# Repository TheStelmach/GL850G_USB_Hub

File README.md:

Board made primarily for evaluation of the GL852G IC that was at the time being considered for a larger PCB design.
Contains one High-Speed upstream port and four independent downstream HS/FS ports with MTT.

Designed for easy hand assembly, with only two 0402 capacitors for crystal. All bootstrapping and IO pins are easily accessible on the board.

Components are only placed on top layer.

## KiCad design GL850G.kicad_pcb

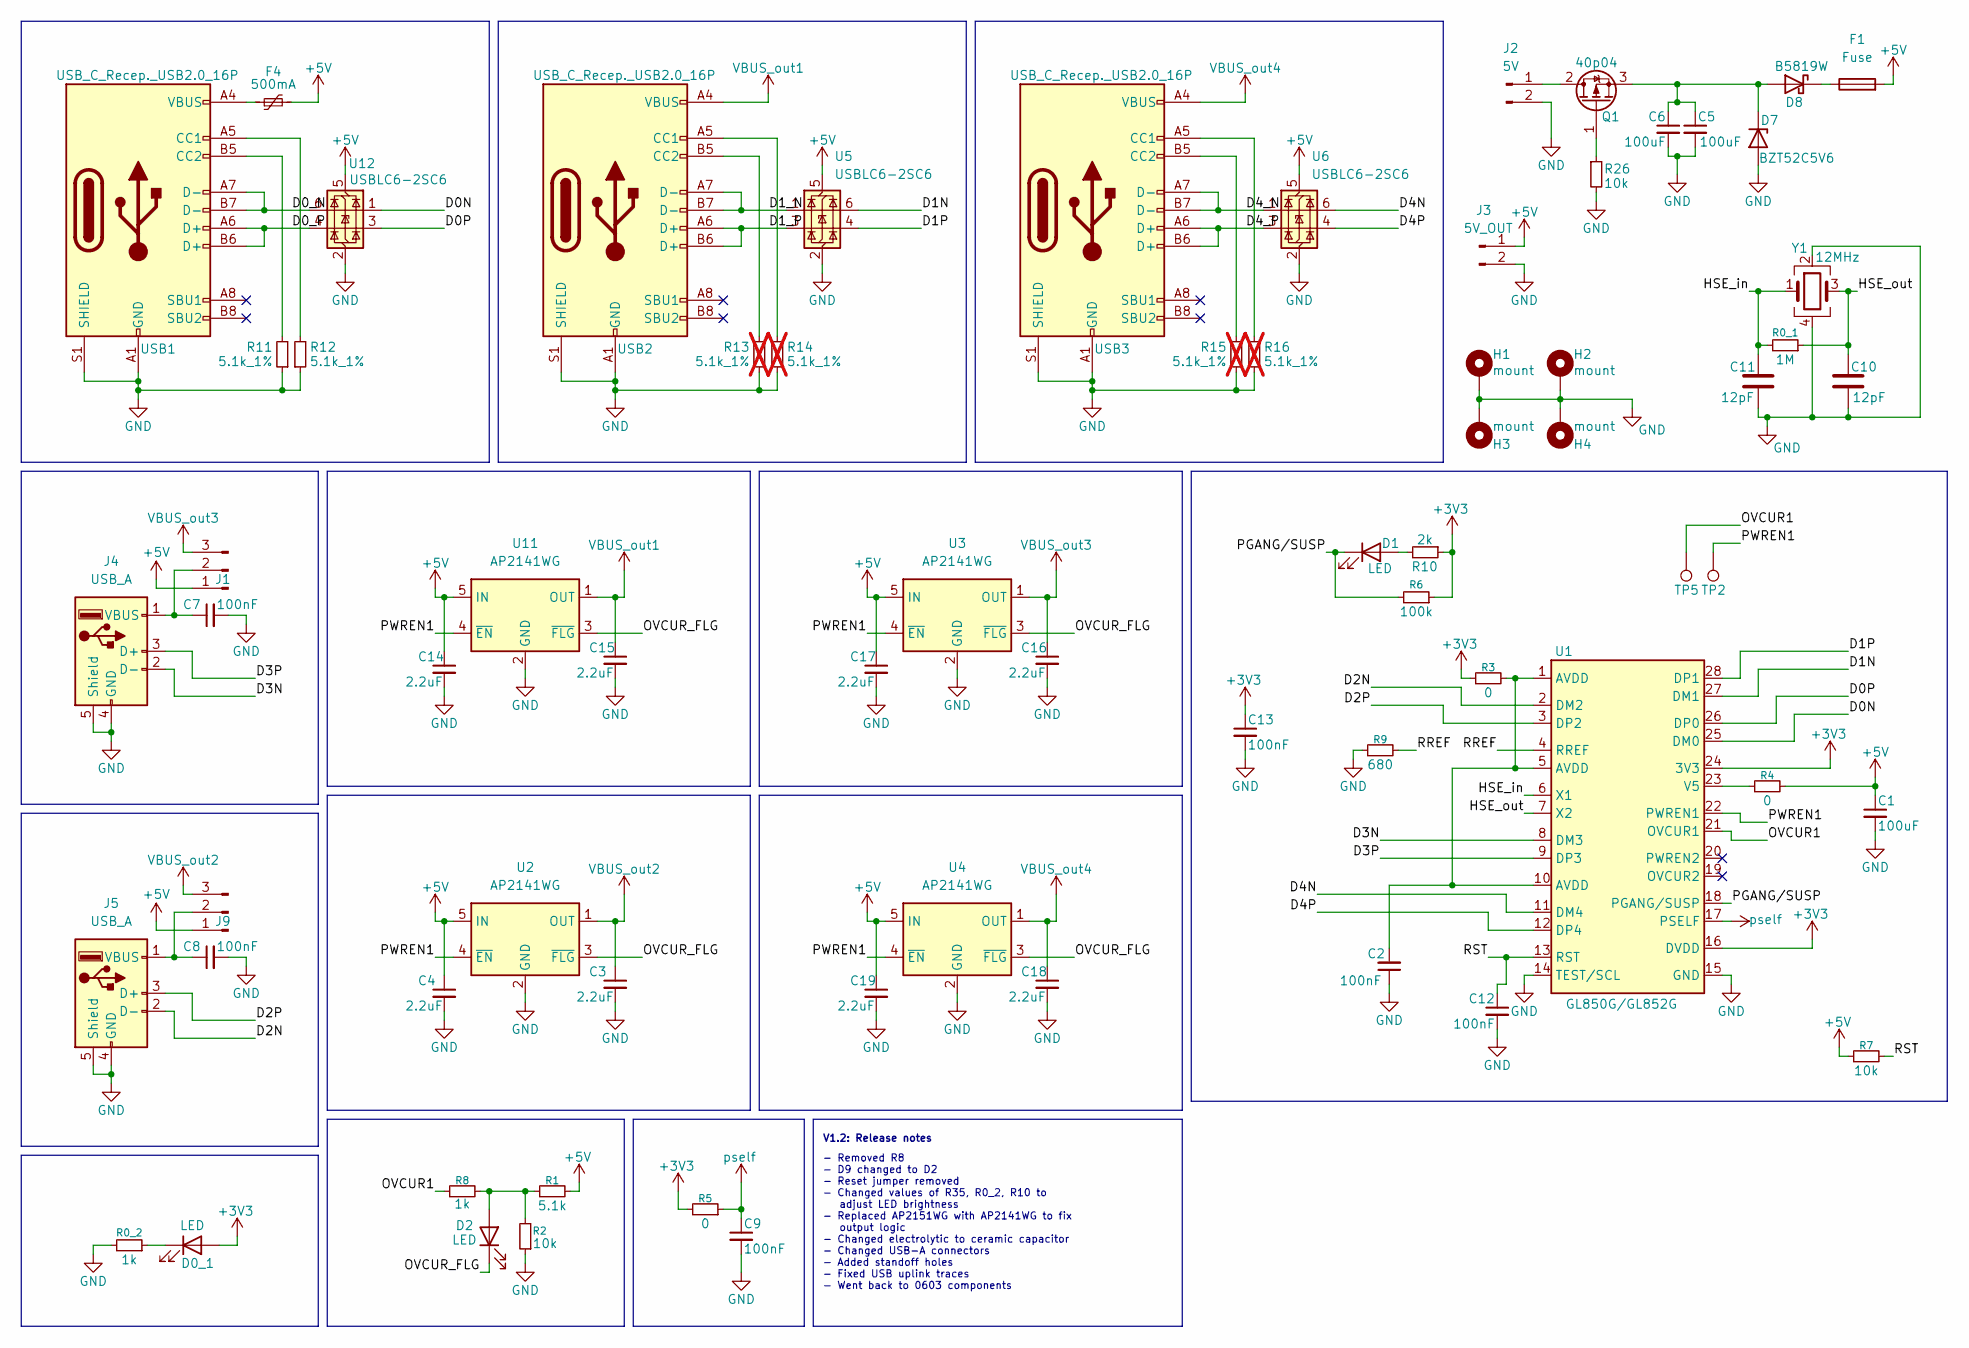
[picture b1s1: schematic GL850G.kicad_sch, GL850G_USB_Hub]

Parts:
C1, C5, C6: 100uF; C_1206_3216Metric_Pad1.33x1.80mm_HandSolder
C2, C7, C8, C9, C12, C13: 100nF; C_0603_1608Metric_Pad1.08x0.95mm_HandSolder
C3, C4, C14, C15, C16, C17, C18, C19: 2.2uF; C_0603_1608Metric_Pad1.08x0.95mm_HandSolder
C10, C11: 12pF; C_0402_1005Metric_Pad0.74x0.62mm_HandSolder
D0_1, D1, D2: LED; LED_0805_2012Metric_Pad1.15x1.40mm_HandSolder
D7: BZT52C5V6; D_SOD-123
D8: B5819W; D_SOD-123
F1: Fuse; Fuseholder_Littelfuse_Nano2_154x
F4: 500mA; Fuse_0805_2012Metric
H1, H2, H3, H4: mount; Standoff_M2
J1, J9: Conn_01x03_Pin; PinHeader_1x03_P2.54mm_Vertical
J2: 5V; JST_XH_B2B-XH-A_1x02_P2.50mm_Vertical
J3: 5V_OUT; PinHeader_1x02_P2.54mm_Vertical
J4, J5: USB_A; USB_2.0_TYPE_A_RECESSED
Q1: 40p04; TO-252-2
R0_1: 1M; R_0805_2012Metric_Pad1.20x1.40mm_HandSolder
R0_2: 1k; R_0603_1608Metric_Pad0.98x0.95mm_HandSolder
R1: 5.1k; R_0805_2012Metric_Pad1.20x1.40mm_HandSolder
R2, R7: 10k; R_0805_2012Metric_Pad1.20x1.40mm_HandSolder
R3, R4, R5: 0; R_0805_2012Metric_Pad1.20x1.40mm_HandSolder
R6: 100k; R_0805_2012Metric_Pad1.20x1.40mm_HandSolder
R8: 1k; R_0805_2012Metric_Pad1.20x1.40mm_HandSolder
R9: 680; R_0805_2012Metric_Pad1.20x1.40mm_HandSolder
R10: 2k; R_0805_2012Metric_Pad1.20x1.40mm_HandSolder
R11, R12: 5.1k_1%; R_0603_1608Metric_Pad0.98x0.95mm_HandSolder
R13, R14, R15, R16: 5.1k_1%; R_0603_1608Metric_Pad0.98x0.95mm_HandSolder; not fitted
R26: 10k; R_0603_1608Metric_Pad0.98x0.95mm_HandSolder
TP2, TP5: TestPoint; TestPoint_Pad_D2.0mm
U1: GL850G/GL852G; SSOP-28_5.3x10.2mm_P0.65mm
U2, U3, U4, U11: AP2141WG; SOT-23-5_HandSoldering
U5, U6, U12: USBLC6-2SC6; SOT-23-6
USB1, USB2, USB3: USB_C_Recep._USB2.0_16P; USB_C_Receptacle_GCT_USB4105-xx-A_16P_TopMnt_Horizontal
Y1: 12MHz; Crystal_SMD_3225-4Pin_3.2x2.5mm_HandSoldering

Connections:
+3V3: C13.1, D0_1.2 (A), R3.1, R5.2, R6.1, R10.1, U1.16 (DVDD), U1.24 (3V3)
+5V: C1.1, C4.1, C14.1, C17.1, C19.1, F1.2, F4.2, J1.1, J3.1, J9.1, R1.2, R4.2, R7.1, U2.5 (IN), U3.5 (IN), U4.5 (IN), U5.5 (VBUS), U6.5 (VBUS), U11.5 (IN), U12.5 (VBUS)
/D0N: U1.25 (DM0), U12.1 (I/O1)
/D0P: U1.26 (DP0), U12.3 (I/O2)
/D0_N: U12.6 (I/O1), USB1.A7 (D-), USB1.B7 (D-)
/D0_P: U12.4 (I/O2), USB1.A6 (D+), USB1.B6 (D+)
/D1N: U1.27 (DM1), U5.6 (I/O1)
/D1P: U1.28 (DP1), U5.4 (I/O2)
/D1_N: U5.1 (I/O1), USB2.A7 (D-), USB2.B7 (D-)
/D1_P: U5.3 (I/O2), USB2.A6 (D+), USB2.B6 (D+)
/D2N: J5.2 (D-), U1.2 (DM2)
/D2P: J5.3 (D+), U1.3 (DP2)
/D3N: J4.2 (D-), U1.8 (DM3)
/D3P: J4.3 (D+), U1.9 (DP3)
/D4N: U1.11 (DM4), U6.6 (I/O1)
/D4P: U1.12 (DP4), U6.4 (I/O2)
/D4_N: U6.1 (I/O1), USB3.A7 (D-), USB3.B7 (D-)
/D4_P: U6.3 (I/O2), USB3.A6 (D+), USB3.B6 (D+)
/HSE_in: C11.1, R0_1.2, U1.6 (X1), Y1.1
/HSE_out: C10.1, R0_1.1, U1.7 (X2), Y1.3
/OVCUR1: R8.1, TP5.1, U1.21 (OVCUR1)
/OVCUR_FLG: D2.1 (K), U2.3 (~FLG), U3.3 (~FLG), U4.3 (~FLG), U11.3 (~FLG)
/PGANG/SUSP: D1.1 (K), R6.2, U1.18 (PGANG/SUSP)
/PWREN1: TP2.1, U1.22 (PWREN1), U2.4 (~EN), U3.4 (~EN), U4.4 (~EN), U11.4 (~EN)
/RREF: R9.2, U1.4 (RREF)
/RST: C12.1, R7.2, U1.13 (RST)
GND: C1.2, C2.1, C3.2, C4.2, C5.2, C6.2, C7.2, C8.2, C9.2, C10.2, C11.2, C12.2, C13.2, C14.2, C15.2, C16.2, C17.2, C18.2, C19.2, D7.2 (A), H1.1, H2.1, H3.1, H4.1, J2.2, J3.2, J4.4 (GND), J4.5 (Shield), J5.4 (GND), J5.5 (Shield), R0_2.2, R2.1, R9.1, R11.1, R12.1, R13.1, R14.1, R15.1, R16.1, R26.2, U1.14 (TEST/SCL), U1.15 (GND), U2.2 (GND), U3.2 (GND), U4.2 (GND), U5.2 (GND), U6.2 (GND), U11.2 (GND), U12.2 (GND), USB1.A1 (GND), USB1.A12 (GND), USB1.B1 (GND), USB1.B12 (GND), USB1.S1 (SHIELD), USB2.A1 (GND), USB2.A12 (GND), USB2.B1 (GND), USB2.B12 (GND), USB2.S1 (SHIELD), USB3.A1 (GND), USB3.A12 (GND), USB3.B1 (GND), USB3.B12 (GND), USB3.S1 (SHIELD), Y1.2, Y1.4
unnamed: C2.2, R3.2, U1.1 (AVDD), U1.5 (AVDD), U1.10 (AVDD)
unnamed: D0_1.1 (K), R0_2.1
unnamed: D1.2 (A), R10.2
unnamed: D2.2 (A), R1.1, R2.2, R8.2
unnamed: C5.1, C6.1, D7.1 (K), D8.2 (A), Q1.3 (S)
unnamed: D8.1 (K), F1.1
unnamed: F4.1, USB1.A4 (VBUS), USB1.A9 (VBUS), USB1.B4 (VBUS), USB1.B9 (VBUS)
unnamed: C7.1, J1.2, J4.1 (VBUS)
unnamed: J2.1, Q1.2 (D)
unnamed: C8.1, J5.1 (VBUS), J9.2
unnamed: Q1.1 (G), R26.1
unnamed: R4.1, U1.23 (V5)
unnamed: R12.2, USB1.A5 (CC1)
unnamed: R11.2, USB1.B5 (CC2)
unnamed: R14.2, USB2.A5 (CC1)
unnamed: R13.2, USB2.B5 (CC2)
unnamed: R16.2, USB3.A5 (CC1)
unnamed: R15.2, USB3.B5 (CC2)
VBUS_out1: C15.1, U11.1 (OUT), USB2.A4 (VBUS), USB2.A9 (VBUS), USB2.B4 (VBUS), USB2.B9 (VBUS)
VBUS_out2: C3.1, J9.3, U2.1 (OUT)
VBUS_out3: C16.1, J1.3, U3.1 (OUT)
VBUS_out4: C18.1, U4.1 (OUT), USB3.A4 (VBUS), USB3.A9 (VBUS), USB3.B4 (VBUS), USB3.B9 (VBUS)
pself: C9.1, R5.1, U1.17 (PSELF)

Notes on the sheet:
V1.2: Release notes
- Removed R8 - D9 changed to D2 - Reset jumper removed - Changed values of R35, R0_2, R10 to adjust LED brightness - Replaced AP2151WG with AP2141WG to fix output logic - Changed electrolytic to ceramic capacitor - Changed USB-A connectors - Added standoff holes - Fixed USB uplink traces - Went bac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

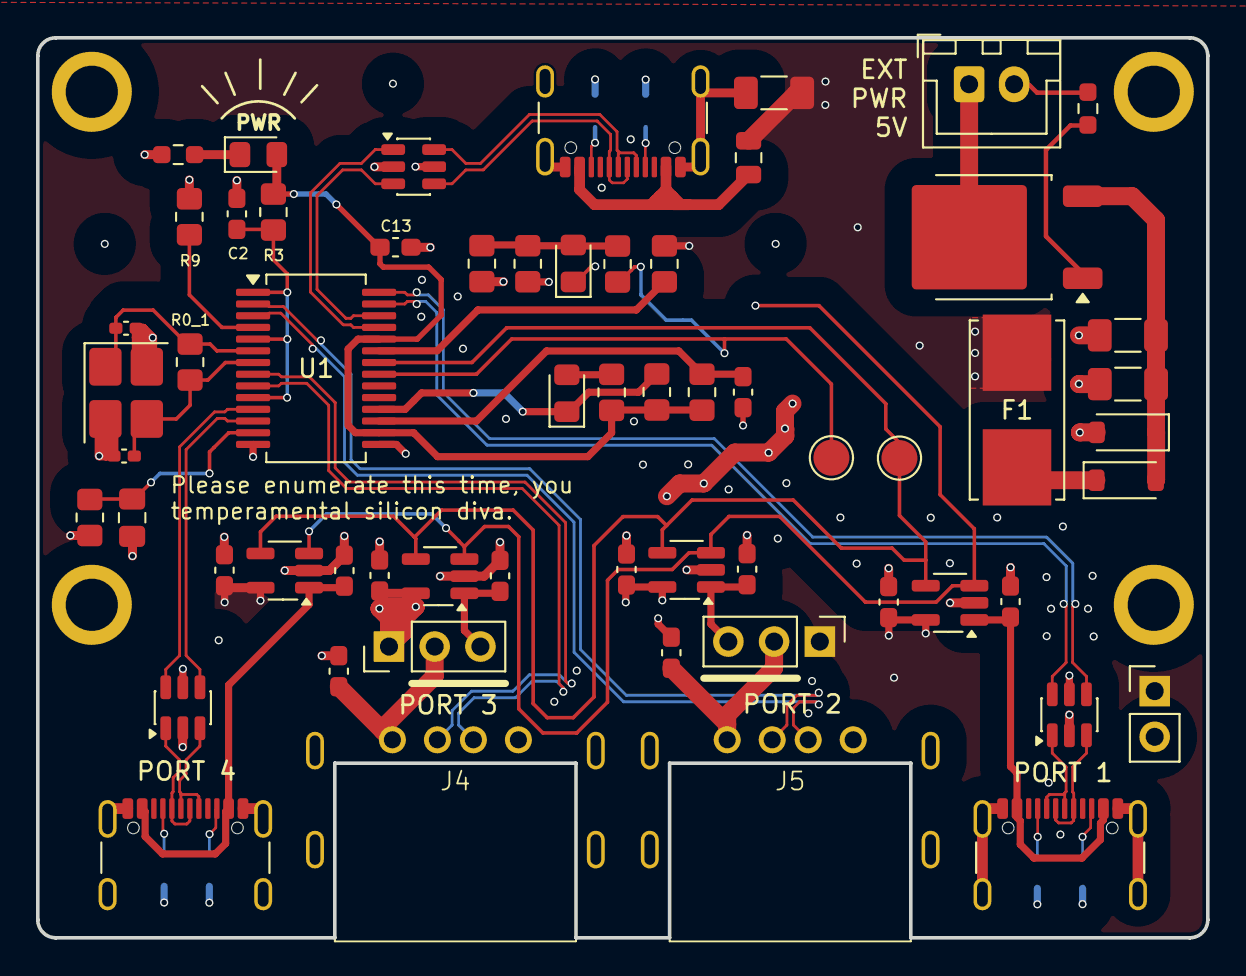
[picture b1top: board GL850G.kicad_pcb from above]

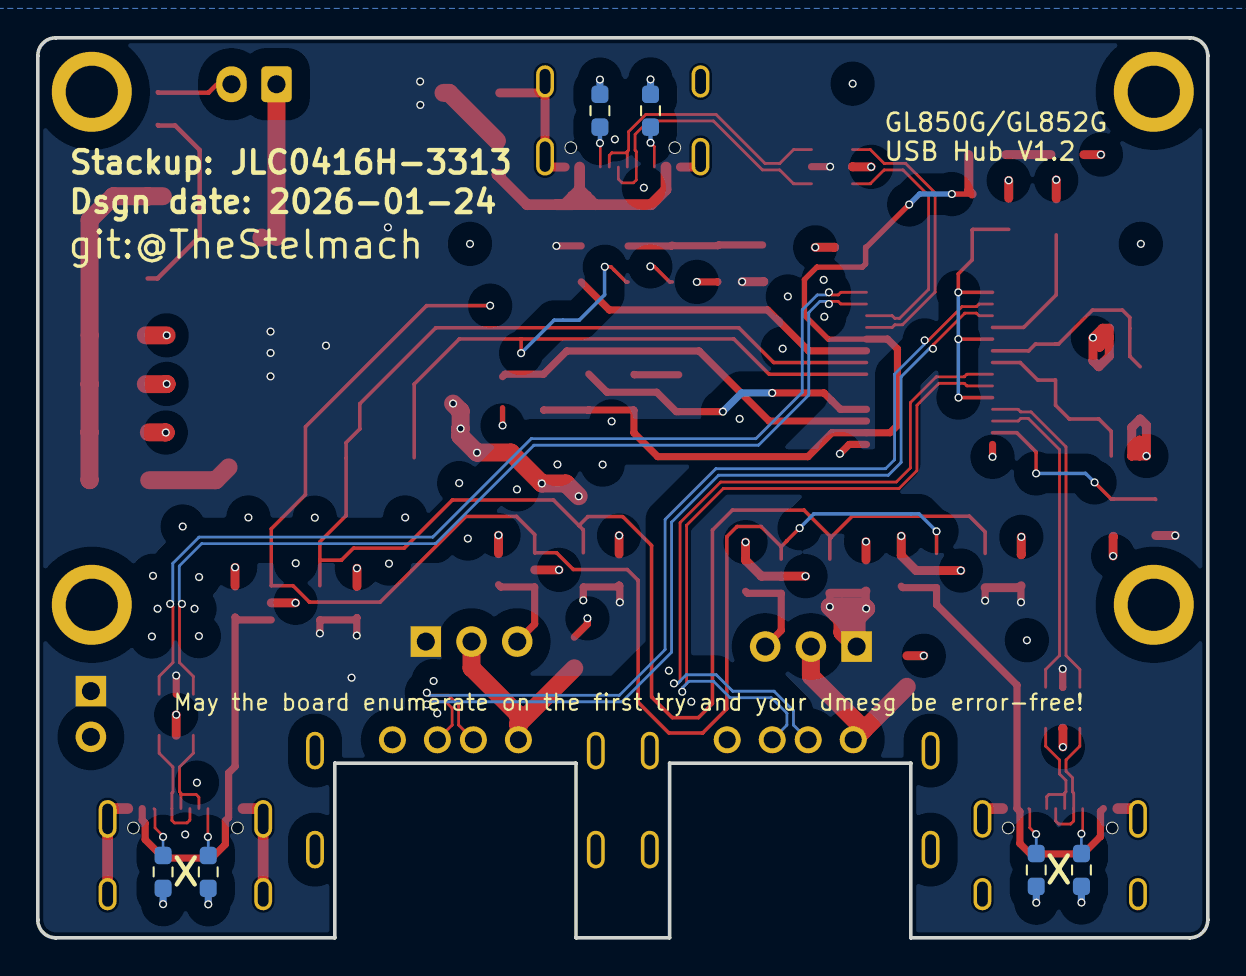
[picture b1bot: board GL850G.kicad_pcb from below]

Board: 4 copper layers, 65.0 x 50.0 mm, 70 parts (10 on the bottom side), 50 nets.

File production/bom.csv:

Designator,Footprint,Quantity,Value,LCSC Part #
"C1, C5, C6",1206,3,100uF,
"C10, C11",0402,2,12pF,
C12,0805,1,100nF,
"C13, C2, C7, C8, C9",0603,5,100nF,
"C14, C15, C16, C17, C18, C19, C3, C4",0603,8,2.2uF,
"D1, D2",0805,2,LED,
D7,D_SOD-123,1,BZT52C5V6,
D8,D_SOD-123,1,B5819W,
F1,Fuseholder_Littelfuse_Nano2_154x,1,Fuse,
F4,0805,1,500mA,
"J1, J9",PinHeader_1x03_P2.54mm_Vertical,2,Conn_01x03_Pin,
J2,JST_XH_B2B-XH-A_1x02_P2.50mm_Vertical,1,5V,
J3,PinHeader_1x02_P2.54mm_Vertical,1,5V_OUT,
"J4, J5",USB_2.0_TYPE_A_RECESSED,2,USB_A,
Q1,TO-252-2,1,40p04,
R0_1,0805,1,1M,
"R1, R8",0805,2,1k,
"R10, R2",0805,2,2k,
R26,0603,1,10k,
"R3, R4, R5",0805,3,0,
R6,0805,1,100k,
R7,0805,1,10k,
R9,0805,1,680,
"TP2, TP5",TestPoint_Pad_D2.0mm,2,TestPoint,
U1,SSOP-28_5.3x10.2mm_P0.65mm,1,GL850G/GL852G,
"U11, U2, U3, U4",SOT-23-5_HandSoldering,4,AP2141WG,
"U12, U5, U6",SOT-23-6,3,USBLC6-2SC6,
"USB1, USB2, USB3",USB_C_Receptacle_GCT_USB4105-xx-A_16P_TopMnt_Horizontal,3,USB_C_Recep._USB2.0_16P,
Y1,Crystal_SMD_3225-4Pin_3.2x2.5mm_HandSoldering,1,12MHz,

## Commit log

2025-12-18 Add project description to README.md
2025-12-20 Add back image to README
2025-12-20 Update image size for GL850G_back in README
2025-12-20 Update README.md
    Updated image size for GL850G in README.
2025-12-30 deleted: GL850G-backups/GL850G-2025-12-08_201710.zip deleted: GL850G-backups/GL850G-2025-12-08_202241.zip deleted: GL850G-backups/GL850G-2025-12-08_202819.zip deleted: GL850G-backups/GL850G-2025-12-0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
2026-01-04 modified: 0.My_Library.bak modified: 0.My_Library.kicad_sym new file: GL850G-backups/GL850G-2026-01-02_150657.zip new file: GL850G-backups/GL850G-2026-01-02_151627.zip new file: GL850G-backups/GL850G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
2026-01-04 modified: GL850G.png modified: GL850G_back.png new file: ~GL850G.kicad_pcb.lck deleted: ~GL850G.kicad_pcb.lck
2026-01-04 new file: 0.My_footprint_library.pretty/Standoff_M2.kicad_mod new file: 0.My_footprint_library.pretty/USB_2.0_TYPE_A_RECESSED.kicad_mod new file: GL850G-backups/GL850G-2026-01-04_175119.zip new file: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
2026-01-24 modified: 0.My_footprint_library.pretty/Standoff_M2.kicad_mod deleted: GL850G-backups/GL850G-2025-12-12_214821.zip deleted: GL850G-backups/GL850G-2025-12-12_220756.zip deleted: GL850G-backups/GL850G-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
